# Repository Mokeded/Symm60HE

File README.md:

# Symm60HE

Symmetrical Hall-effect Alice keyboard derived from FN40HE. The production
design uses two keyboard halves connected by 12-conductor FFCs to one compact
AT32F405 daughterboard.

This tree intentionally contains only the files used to build or manufacture
the current ribbon-connected PCBs, plates, populated 3D reference assembly and
firmware. Historical routing iterations, pogo concepts, renders, caches and
intermediate CAD meshes were removed from this directory.

## Authoritative PCB projects

- `pcb/Symm60HE-Panel.kicad_pro`: universal left/right customer panel.
- `pcb/Symm60HE-Daughterboard.kicad_pro`: controller daughterboard.
- `pcb/variants/layouts/<layout>/*-Panel.kicad_pro`: eight fixed-layout
  customer panels.

The `Symm60HE-Left.kicad_pcb`, `Symm60HE-Right.kicad_pcb` and fixed-layout
`*-Left.kicad_pcb`/`*-Right.kicad_pcb` files are retained as mechanical and
generator inputs. The matching `*-Panel` project is the electrical and
manufacturing authority for each pair.

Current fabrication packages are under:

- `release/jlcpcb/`
- `release/layout-pcbs/`

## Plate sets

Manufacture plates from 1.5 mm POM. `plate/` contains a left/right plate pair
and one matching eight-pad Poron gasket DXF for every PCB layout:

| Layout stem | Left bottom row | Right bottom row | Backspace |
|---|---|---|---|
| `wkl` | two 1.5u | standard | split |
| `wkl-left-arrows-right` | two 1.5u | arrows | split |
| `three-key-left-wkl-right` | three 1u | standard | split |
| `wklarrows` | three 1u | arrows | split |
| `wklbs2` | two 1.5u | standard | 2u |
| `wkl-left-arrows-right-bs2` | two 1.5u | arrows | 2u |
| `three-key-left-wkl-right-bs2` | three 1u | standard | 2u |
| `wklbs2arrows` | three 1u | arrows | 2u |
| `universal` | all supported positions | all supported positions | both |

See `plate/README.md` for fabrication and mounting details.

## 3D reference assembly

`case/fusion360/` contains the final editable FreeCAD/Fusion handoff, combined
STEP assembly, separate named component STEP bodies, exact 1.5 mm plates,
verified switch and keycap references, and the source component models needed
to rebuild them. Manufacturing panel rails and mouse-bite tabs are not part of
the case assembly; the 3D reference represents the two depanelized halves.

The locked vertical datum is 5.00 mm from plate top to PCB top.

## Firmware

`firmware/libhmk/` is the Symm60HE firmware source. The current AT32F405 target
is selected by the `symm60he` PlatformIO environment. Distributable firmware
outputs are copied to `firmware/build/`.

## Rebuild

Requirements include Python 3, KiCad 10 CLI/Python, OpenSCAD, FreeCAD command
line tools and PlatformIO.

```sh
python3 -m venv .venv
.venv/bin/pip install -r requirements.txt
./build.sh
```

The build regenerates all nine plate sets, the populated 3D reference, the
universal and fixed-layout fabrication packages, validation reports and the
current firmware binaries. It does not regenerate historical prototypes.

## Licensing and provenance

GPLv3. See `LICENSE`, `NOTICE.md` and the model provenance files under
`case/fusion360/models/`.

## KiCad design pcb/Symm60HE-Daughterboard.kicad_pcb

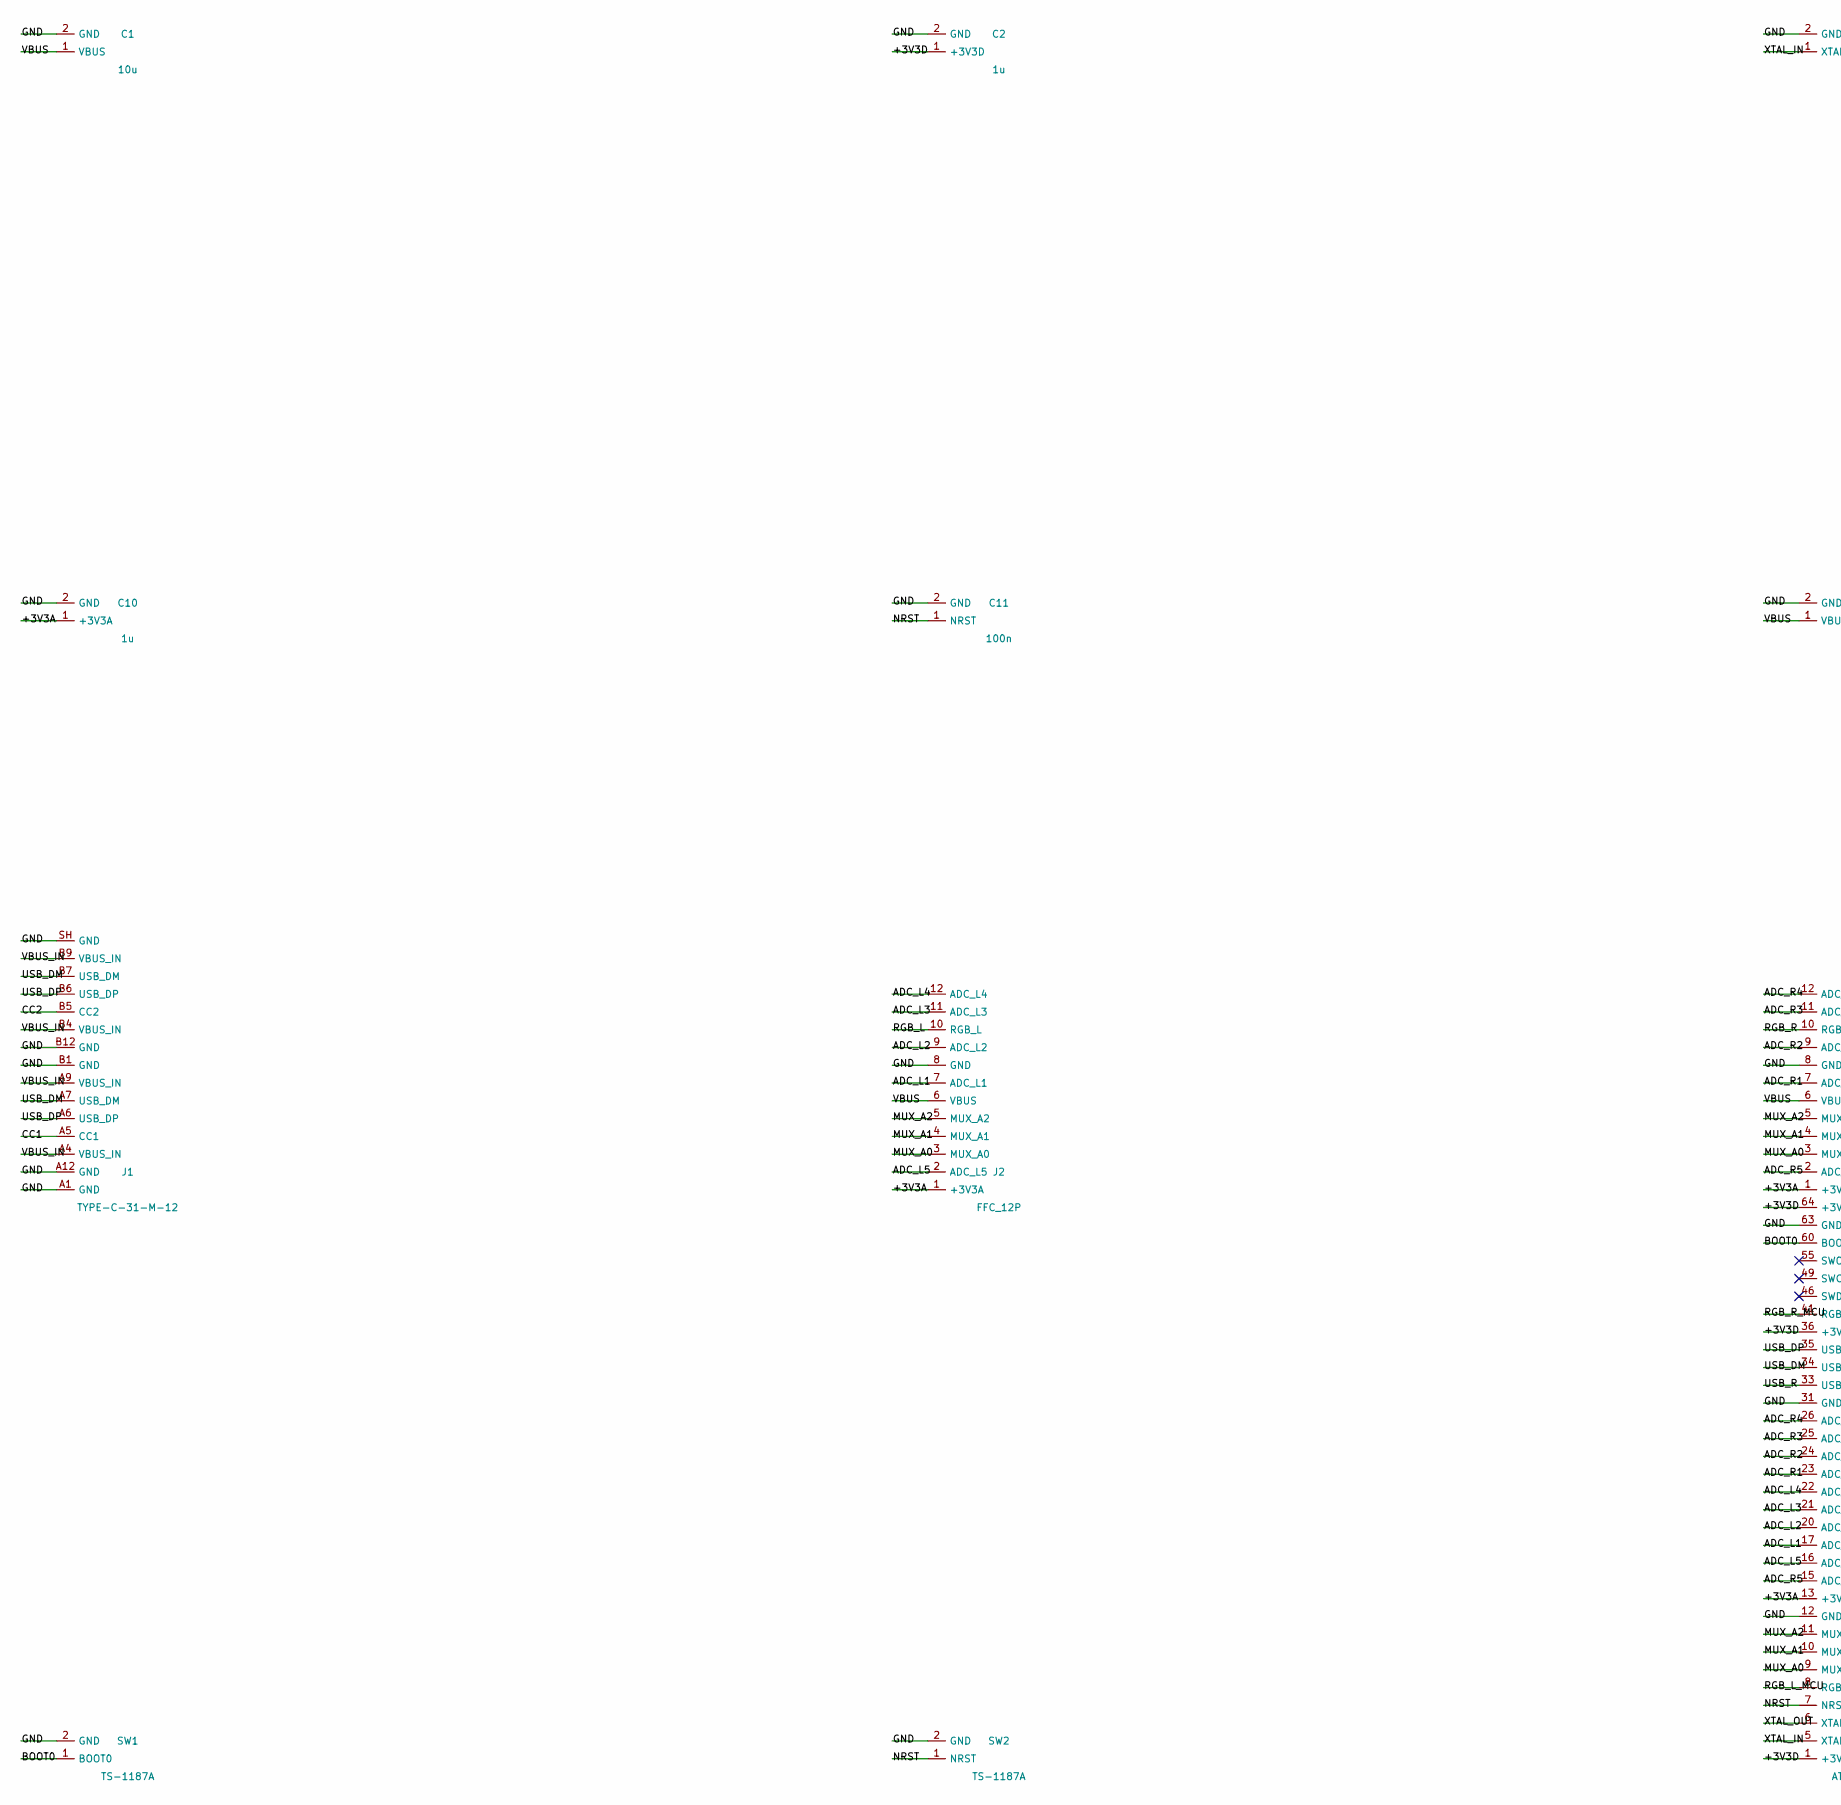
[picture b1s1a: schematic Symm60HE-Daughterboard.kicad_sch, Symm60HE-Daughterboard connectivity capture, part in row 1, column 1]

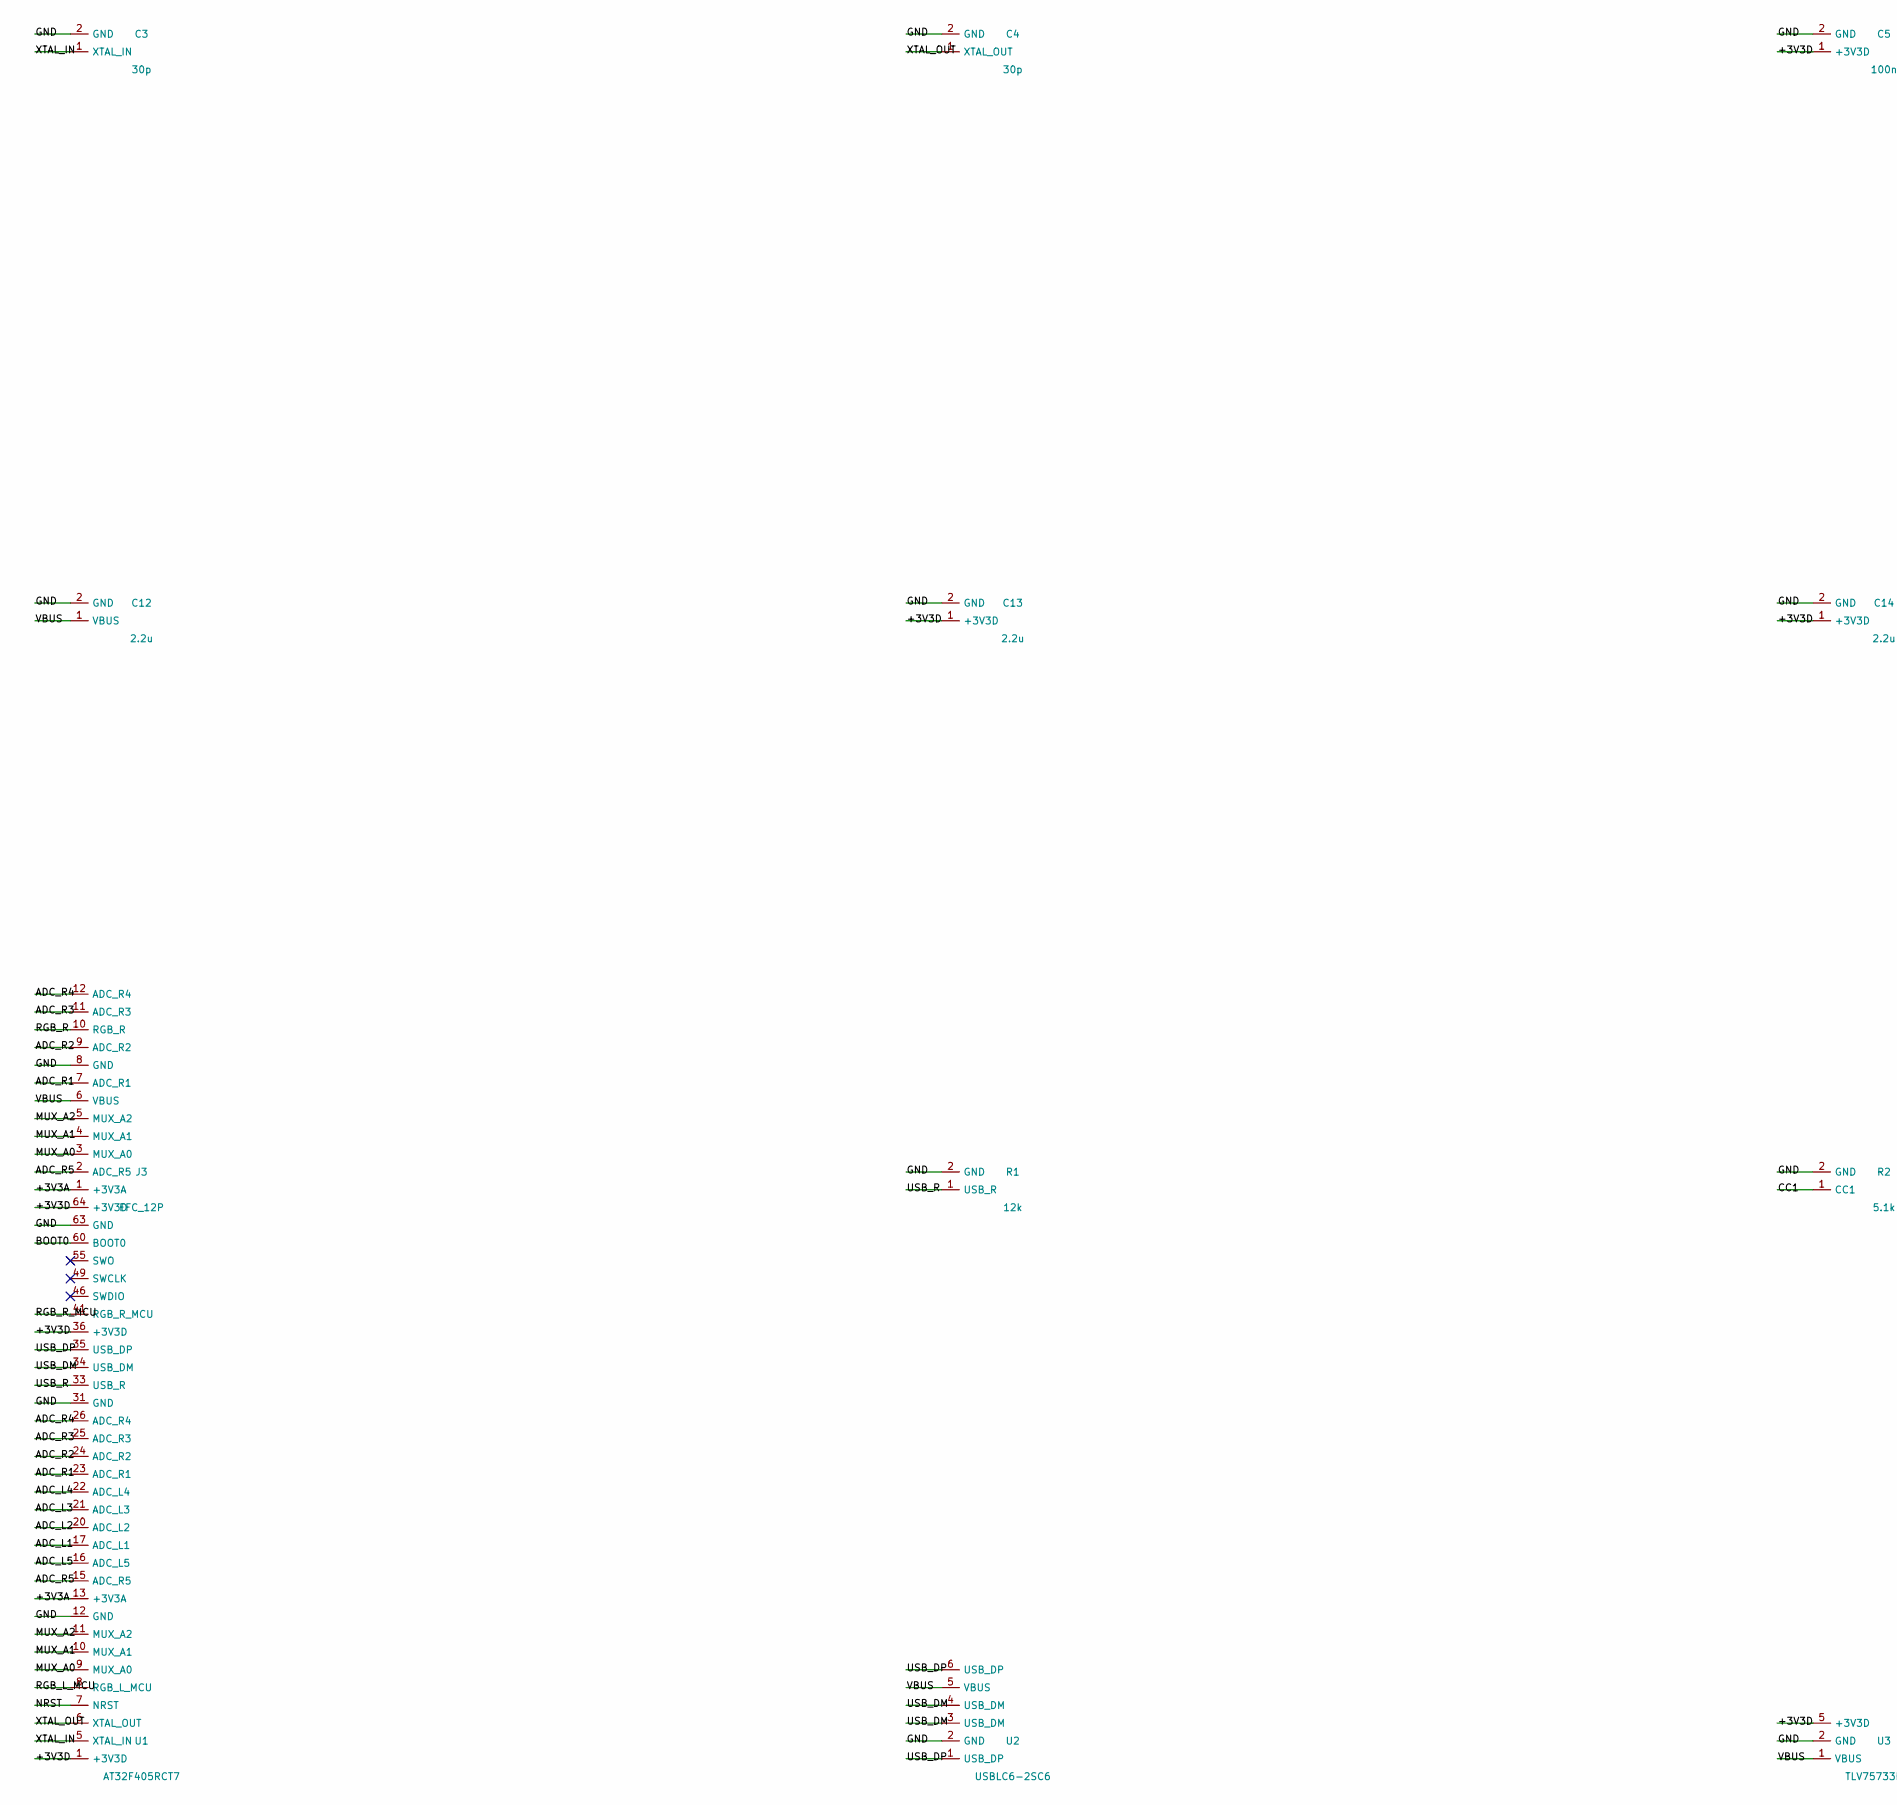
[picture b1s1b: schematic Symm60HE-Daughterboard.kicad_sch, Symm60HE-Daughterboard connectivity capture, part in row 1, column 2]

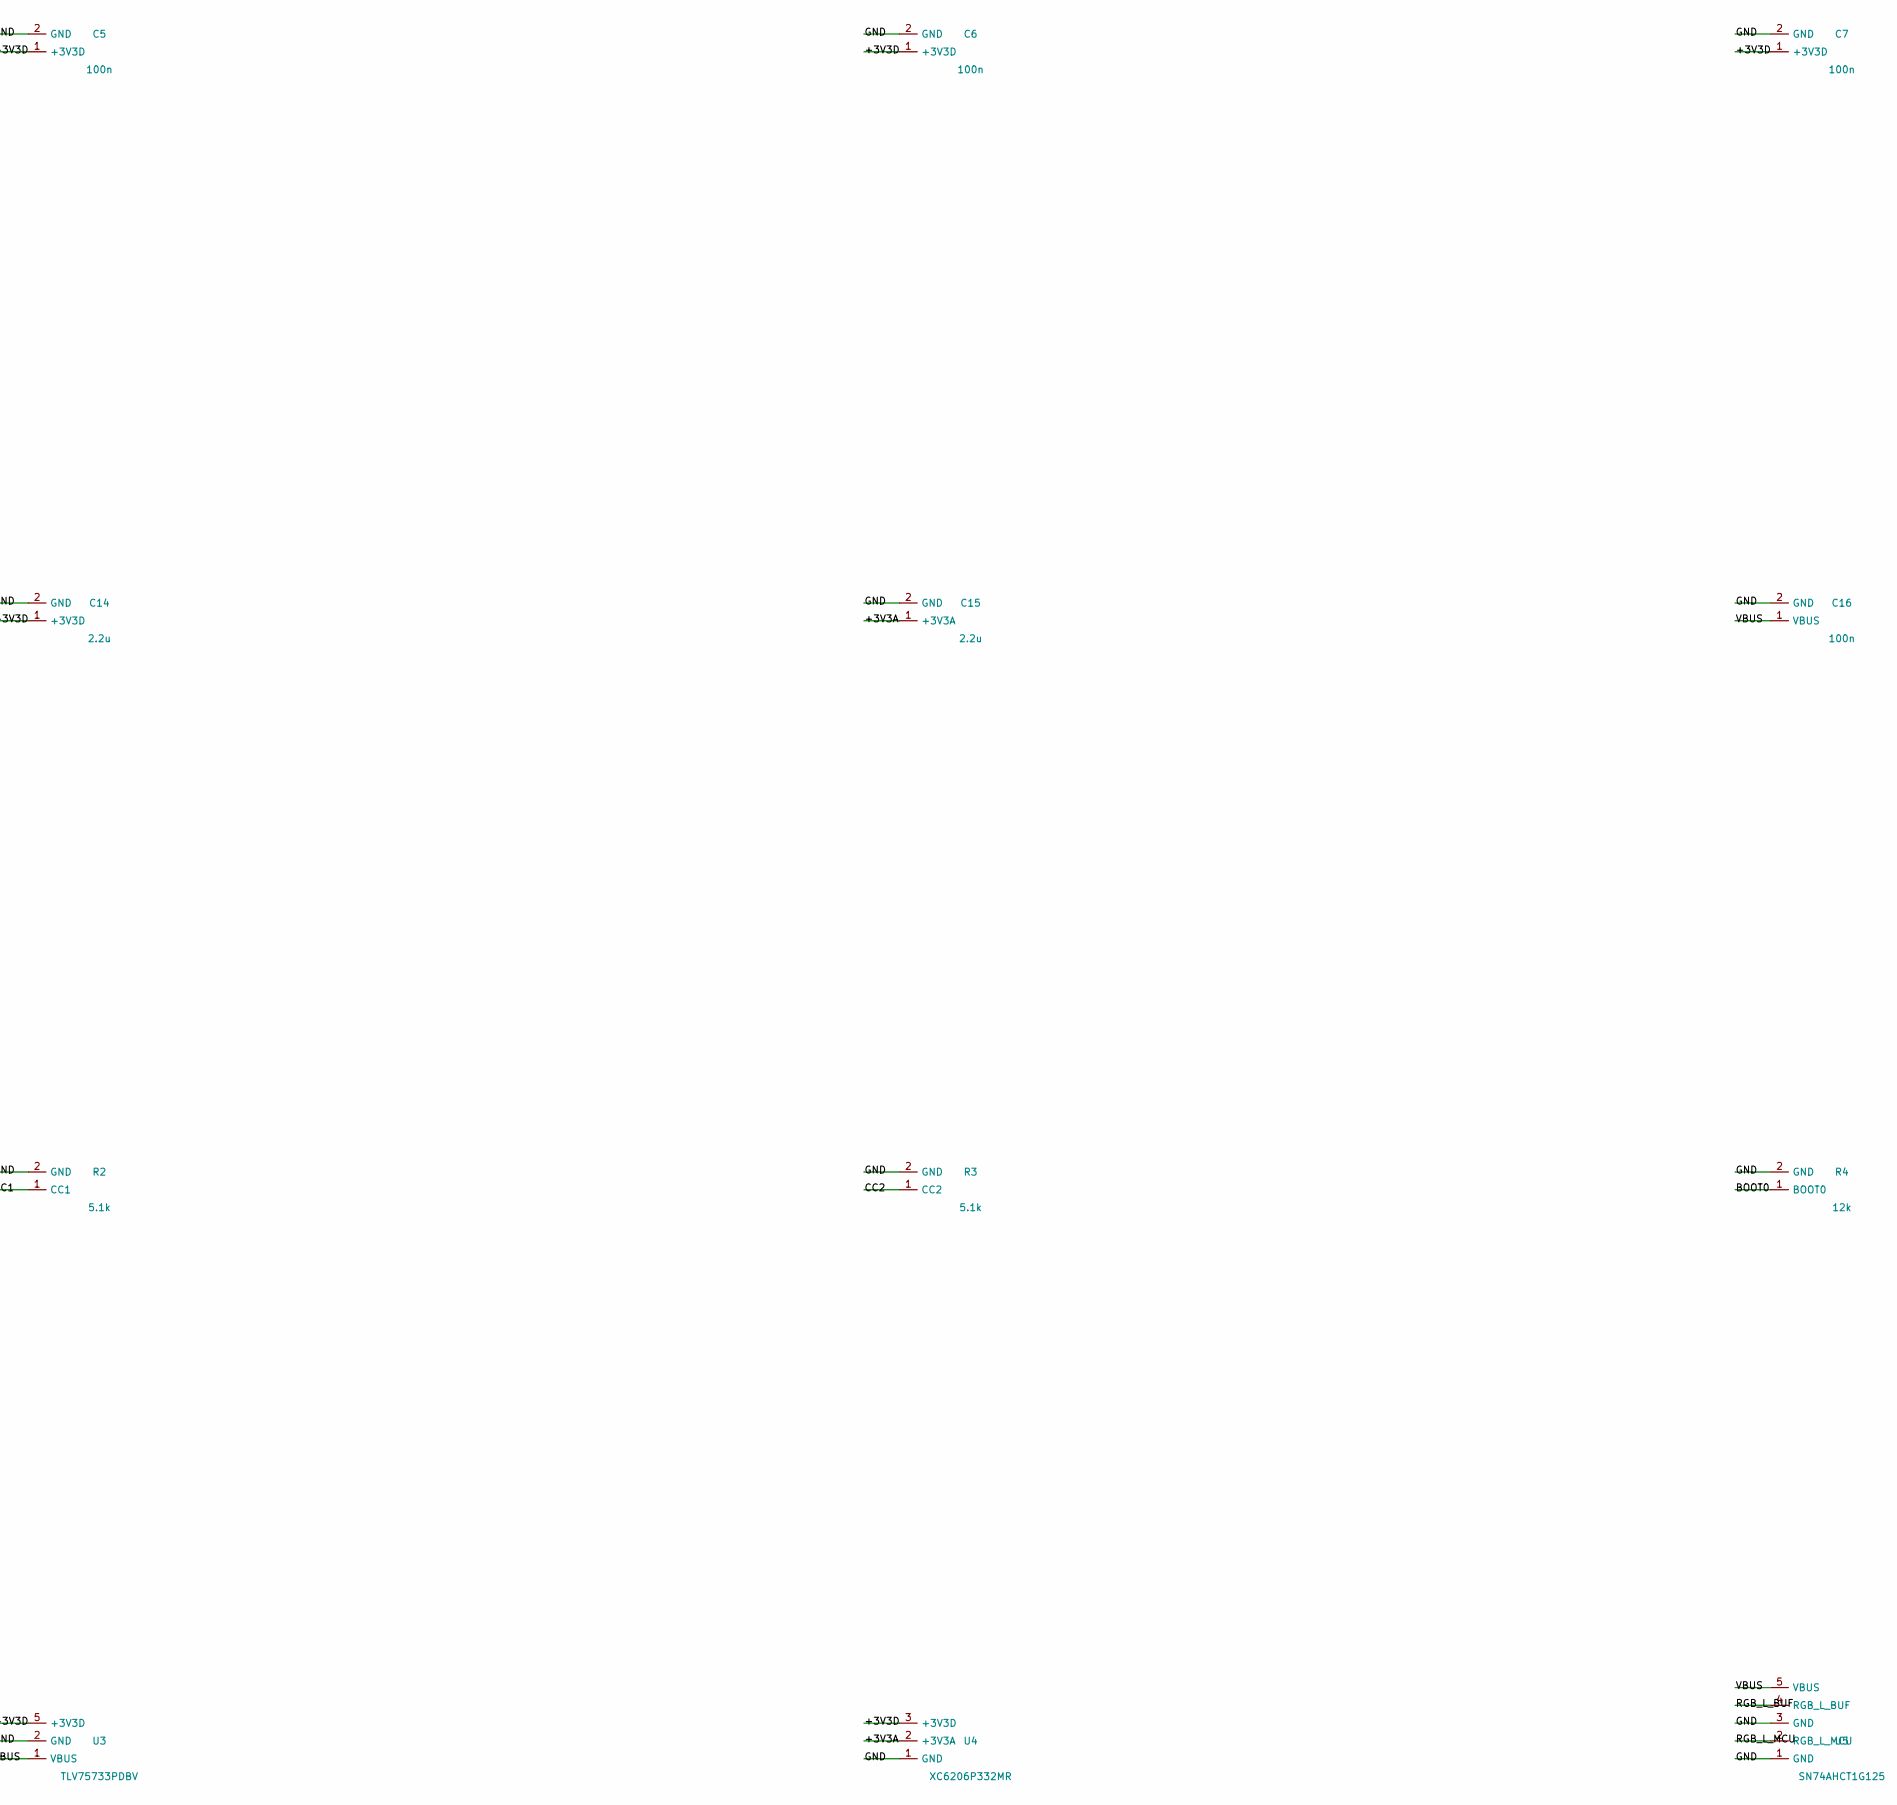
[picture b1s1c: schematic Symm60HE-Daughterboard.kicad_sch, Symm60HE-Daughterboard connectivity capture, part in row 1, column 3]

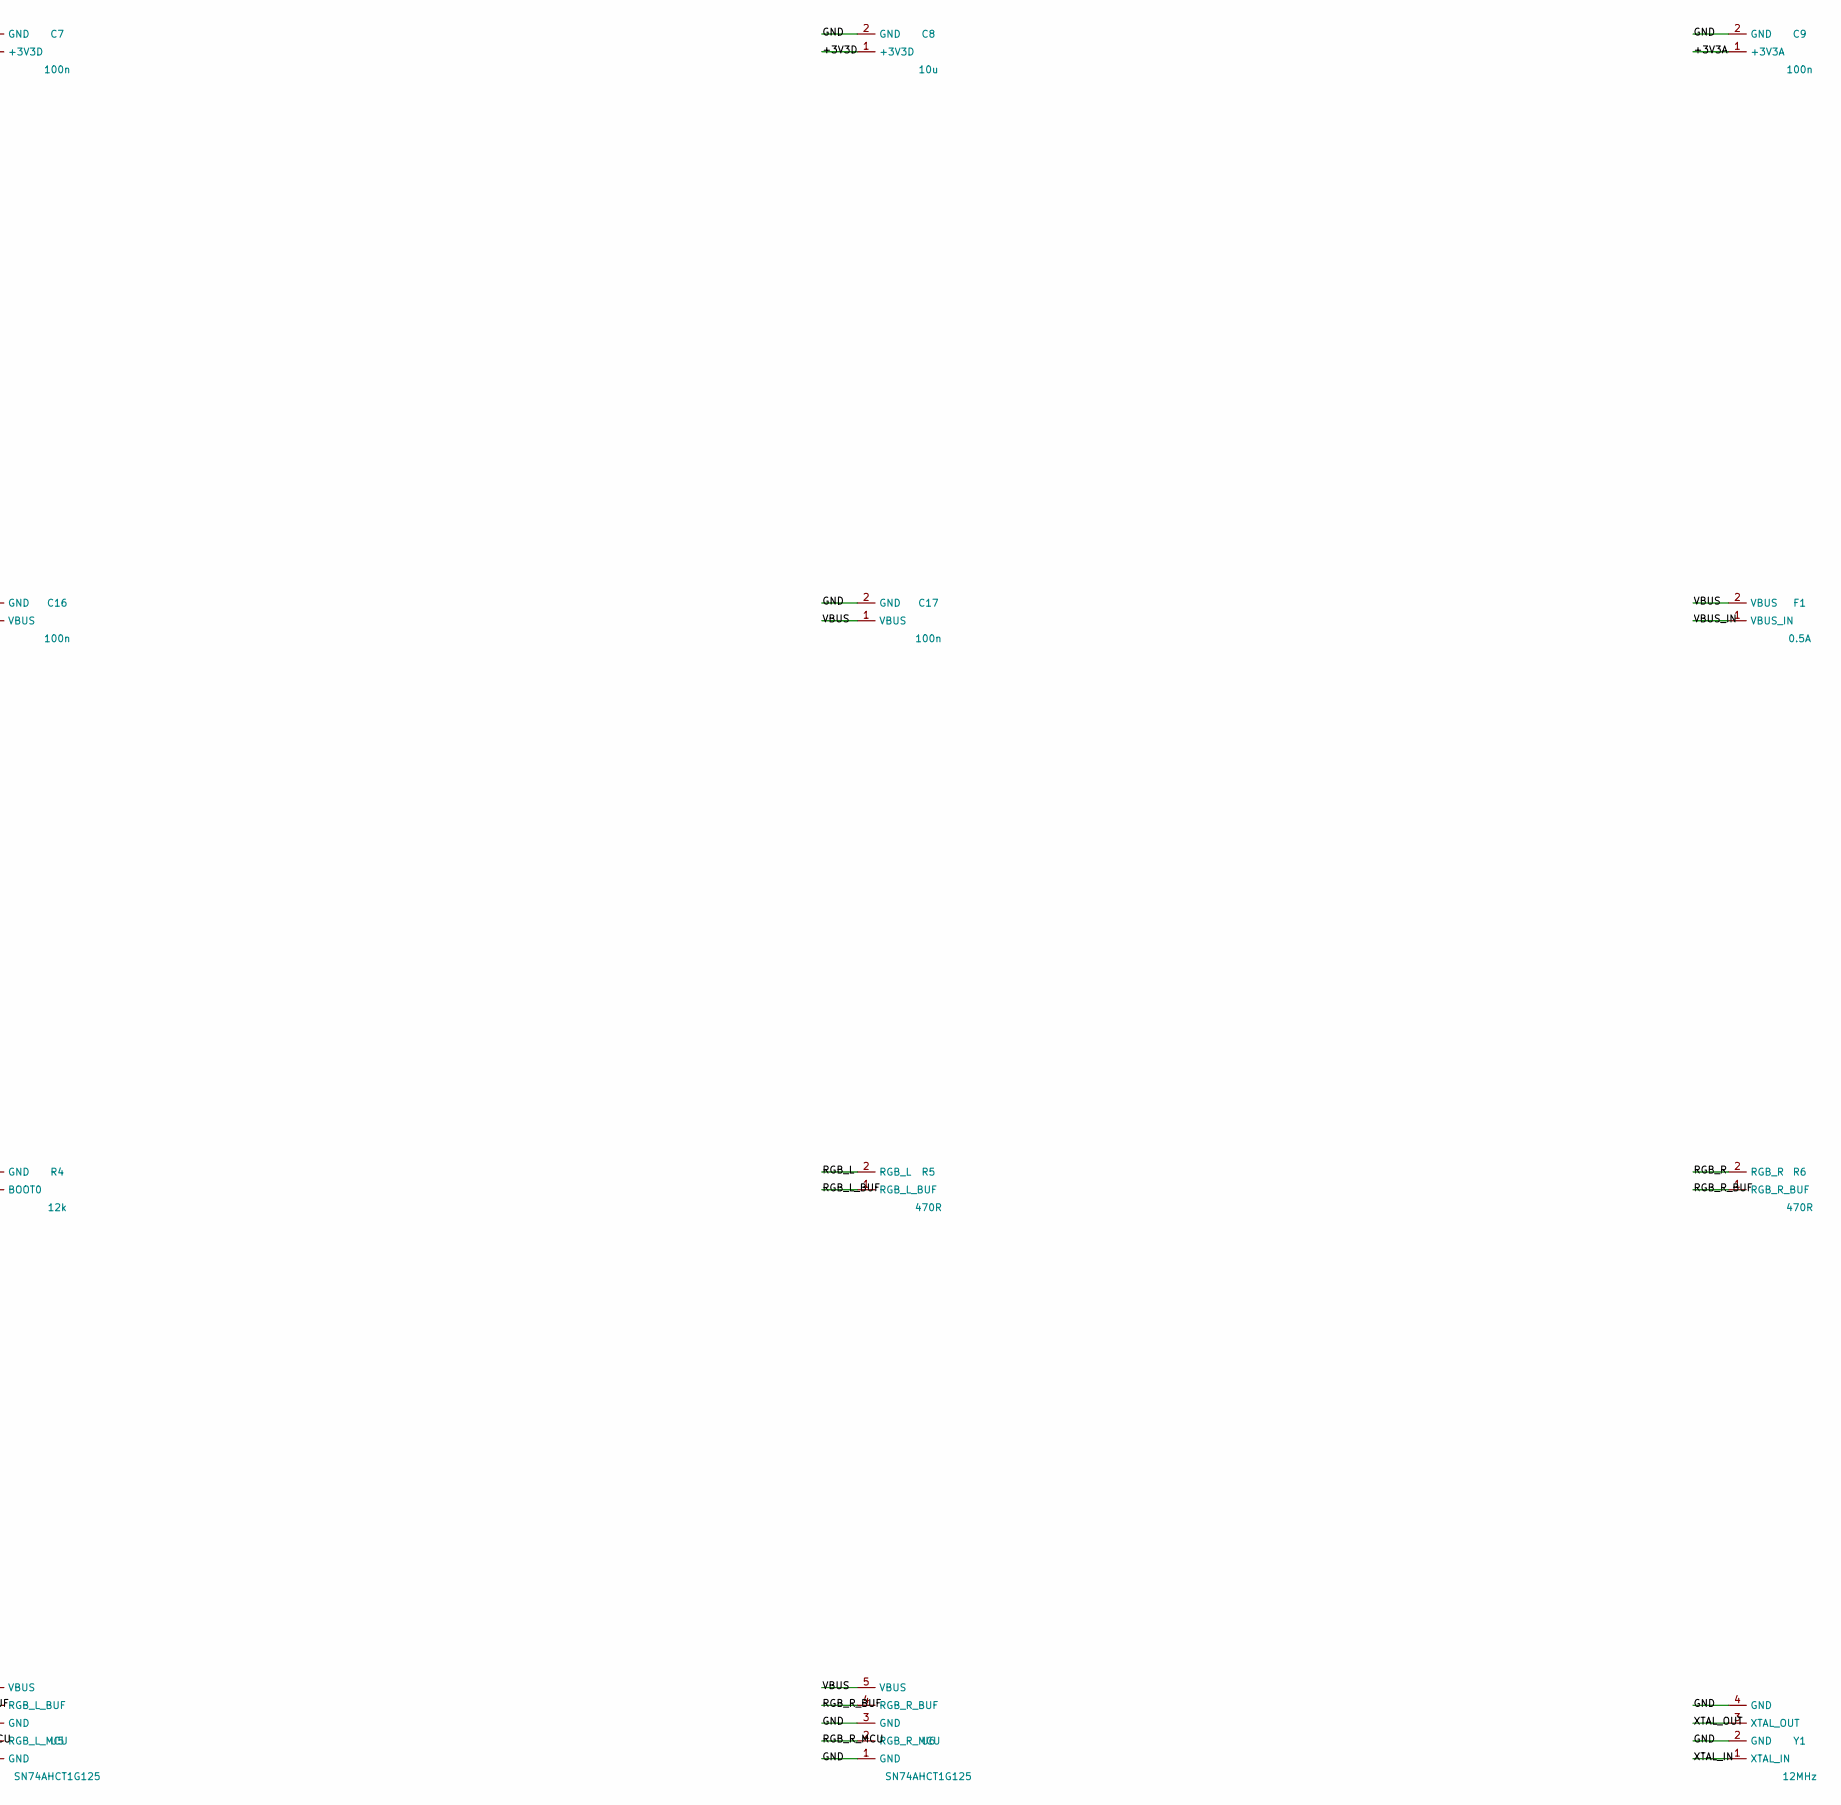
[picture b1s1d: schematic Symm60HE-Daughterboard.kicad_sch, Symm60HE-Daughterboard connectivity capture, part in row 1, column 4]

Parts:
C1, C8: 10u
C2, C10: 1u
C3, C4: 30p
C5, C6, C7, C9, C11, C16, C17: 100n
C12, C13, C14, C15: 2.2u
F1: 0.5A
J1: TYPE-C-31-M-12
J2, J3: FFC_12P
R1, R4: 12k
R2, R3: 5.1k
R5, R6: 470R
SW1, SW2: TS-1187A
U1: AT32F405RCT7
U2: USBLC6-2SC6
U3: TLV75733PDBV
U4: XC6206P332MR
U5, U6: SN74AHCT1G125
Y1: 12MHz

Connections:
+3V3A: C9.1 (+3V3A), C10.1 (+3V3A), C15.1 (+3V3A), J2.1 (+3V3A), J3.1 (+3V3A), U1.13 (+3V3A), U4.2 (+3V3A)
+3V3D: C2.1 (+3V3D), C5.1 (+3V3D), C6.1 (+3V3D), C7.1 (+3V3D), C8.1 (+3V3D), C13.1 (+3V3D), C14.1 (+3V3D), U1.1 (+3V3D), U1.36 (+3V3D), U1.64 (+3V3D), U3.5 (+3V3D), U4.3 (+3V3D)
ADC_L1: J2.7 (ADC_L1), U1.17 (ADC_L1)
ADC_L2: J2.9 (ADC_L2), U1.20 (ADC_L2)
ADC_L3: J2.11 (ADC_L3), U1.21 (ADC_L3)
ADC_L4: J2.12 (ADC_L4), U1.22 (ADC_L4)
ADC_L5: J2.2 (ADC_L5), U1.16 (ADC_L5)
ADC_R1: J3.7 (ADC_R1), U1.23 (ADC_R1)
ADC_R2: J3.9 (ADC_R2), U1.24 (ADC_R2)
ADC_R3: J3.11 (ADC_R3), U1.25 (ADC_R3)
ADC_R4: J3.12 (ADC_R4), U1.26 (ADC_R4)
ADC_R5: J3.2 (ADC_R5), U1.15 (ADC_R5)
BOOT0: R4.1 (BOOT0), SW1.1 (BOOT0), U1.60 (BOOT0)
CC1: J1.A5 (CC1), R2.1 (CC1)
CC2: J1.B5 (CC2), R3.1 (CC2)
GND: C1.2 (GND), C2.2 (GND), C3.2 (GND), C4.2 (GND), C5.2 (GND), C6.2 (GND), C7.2 (GND), C8.2 (GND), C9.2 (GND), C10.2 (GND), C11.2 (GND), C12.2 (GND), C13.2 (GND), C14.2 (GND), C15.2 (GND), C16.2 (GND), C17.2 (GND), J1.A1 (GND), J1.A12 (GND), J1.B1 (GND), J1.B12 (GND), J1.SH (GND), J2.8 (GND), J3.8 (GND), R1.2 (GND), R2.2 (GND), R3.2 (GND), R4.2 (GND), SW1.2 (GND), SW2.2 (GND), U1.12 (GND), U1.31 (GND), U1.63 (GND), U2.2 (GND), U3.2 (GND), U4.1 (GND), U5.1 (GND), U5.3 (GND), U6.1 (GND), U6.3 (GND), Y1.2 (GND), Y1.4 (GND)
MUX_A0: J2.3 (MUX_A0), J3.3 (MUX_A0), U1.9 (MUX_A0)
MUX_A1: J2.4 (MUX_A1), J3.4 (MUX_A1), U1.10 (MUX_A1)
MUX_A2: J2.5 (MUX_A2), J3.5 (MUX_A2), U1.11 (MUX_A2)
NRST: C11.1 (NRST), SW2.1 (NRST), U1.7 (NRST)
RGB_L: J2.10 (RGB_L), R5.2 (RGB_L)
RGB_L_BUF: R5.1 (RGB_L_BUF), U5.4 (RGB_L_BUF)
RGB_L_MCU: U1.8 (RGB_L_MCU), U5.2 (RGB_L_MCU)
RGB_R: J3.10 (RGB_R), R6.2 (RGB_R)
RGB_R_BUF: R6.1 (RGB_R_BUF), U6.4 (RGB_R_BUF)
RGB_R_MCU: U1.41 (RGB_R_MCU), U6.2 (RGB_R_MCU)
SWCLK: U1.49 (SWCLK)
SWDIO: U1.46 (SWDIO)
SWO: U1.55 (SWO)
USB_DM: J1.A7 (USB_DM), J1.B7 (USB_DM), U1.34 (USB_DM), U2.3 (USB_DM), U2.4 (USB_DM)
USB_DP: J1.A6 (USB_DP), J1.B6 (USB_DP), U1.35 (USB_DP), U2.1 (USB_DP), U2.6 (USB_DP)
USB_R: R1.1 (USB_R), U1.33 (USB_R)
VBUS: C1.1 (VBUS), C12.1 (VBUS), C16.1 (VBUS), C17.1 (VBUS), F1.2 (VBUS), J2.6 (VBUS), J3.6 (VBUS), U2.5 (VBUS), U3.1 (VBUS), U5.5 (VBUS), U6.5 (VBUS)
VBUS_IN: F1.1 (VBUS_IN), J1.A4 (VBUS_IN), J1.A9 (VBUS_IN), J1.B4 (VBUS_IN), J1.B9 (VBUS_IN)
XTAL_IN: C3.1 (XTAL_IN), U1.5 (XTAL_IN), Y1.1 (XTAL_IN)
XTAL_OUT: C4.1 (XTAL_OUT), U1.6 (XTAL_OUT), Y1.3 (XTAL_OUT)

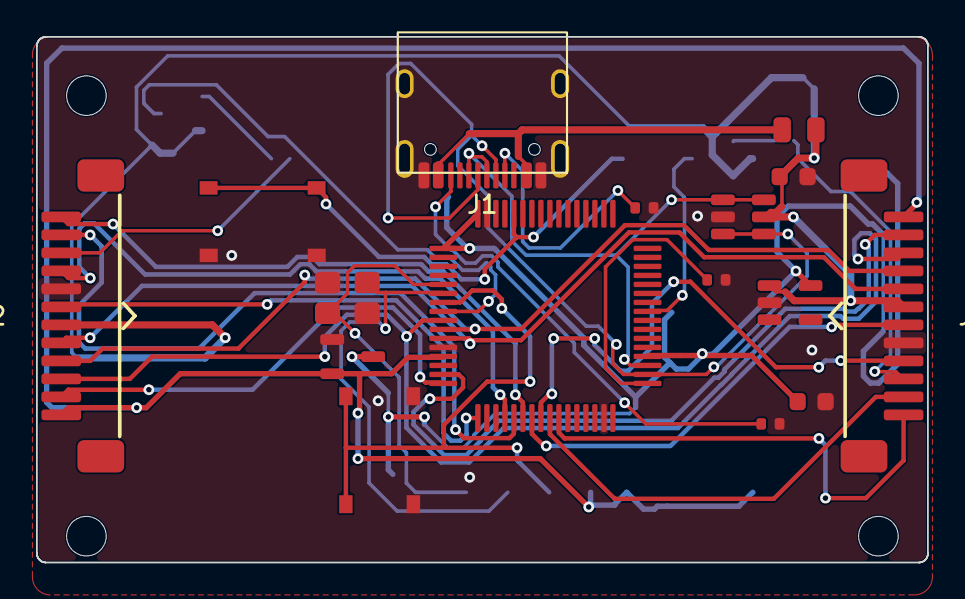
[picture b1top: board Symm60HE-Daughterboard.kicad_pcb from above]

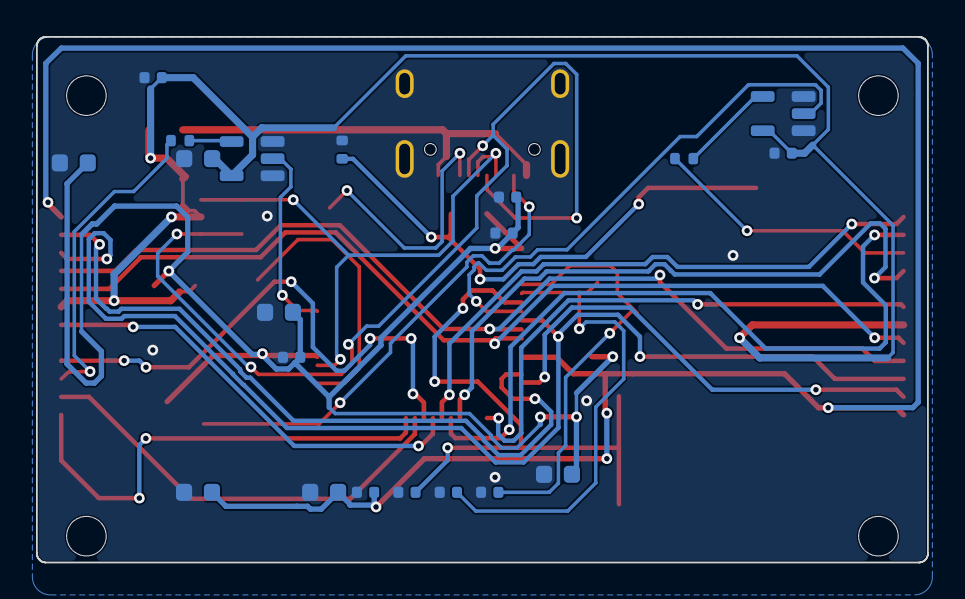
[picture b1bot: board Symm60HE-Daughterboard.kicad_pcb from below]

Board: 2 copper layers, 49.5 x 29.2 mm, 40 parts (20 on the bottom side), 33 nets.

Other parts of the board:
MHD1, MHD2, MHD3, MHD4: M2_NPTH; MountingHole_2.2mm_M2_NPTH
